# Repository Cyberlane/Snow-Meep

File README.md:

Snow-Meep
=========

Soldering is easy Snow Man variant!

A detailed step by step guide (with pictures) will be available later today.

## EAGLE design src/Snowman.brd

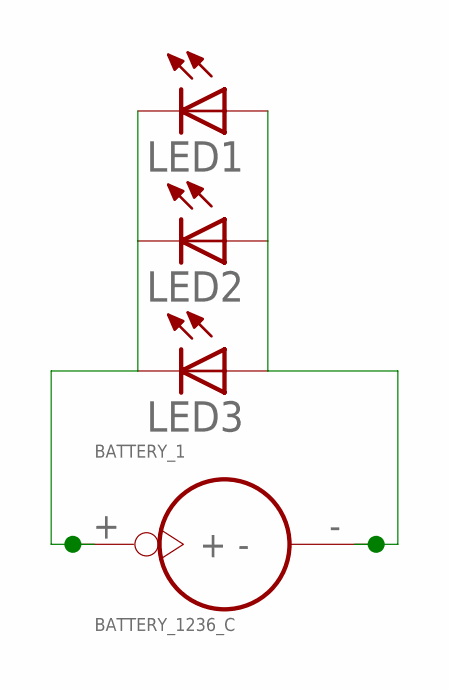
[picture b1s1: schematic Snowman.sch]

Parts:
BATTERY_1: BATTERY_1236_C
LED1, LED2, LED3: LED5MM

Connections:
unnamed: BATTERY_1.+, LED1.K (C), LED2.K (C), LED3.K (C)
unnamed: BATTERY_1.-, LED1.A, LED2.A, LED3.A

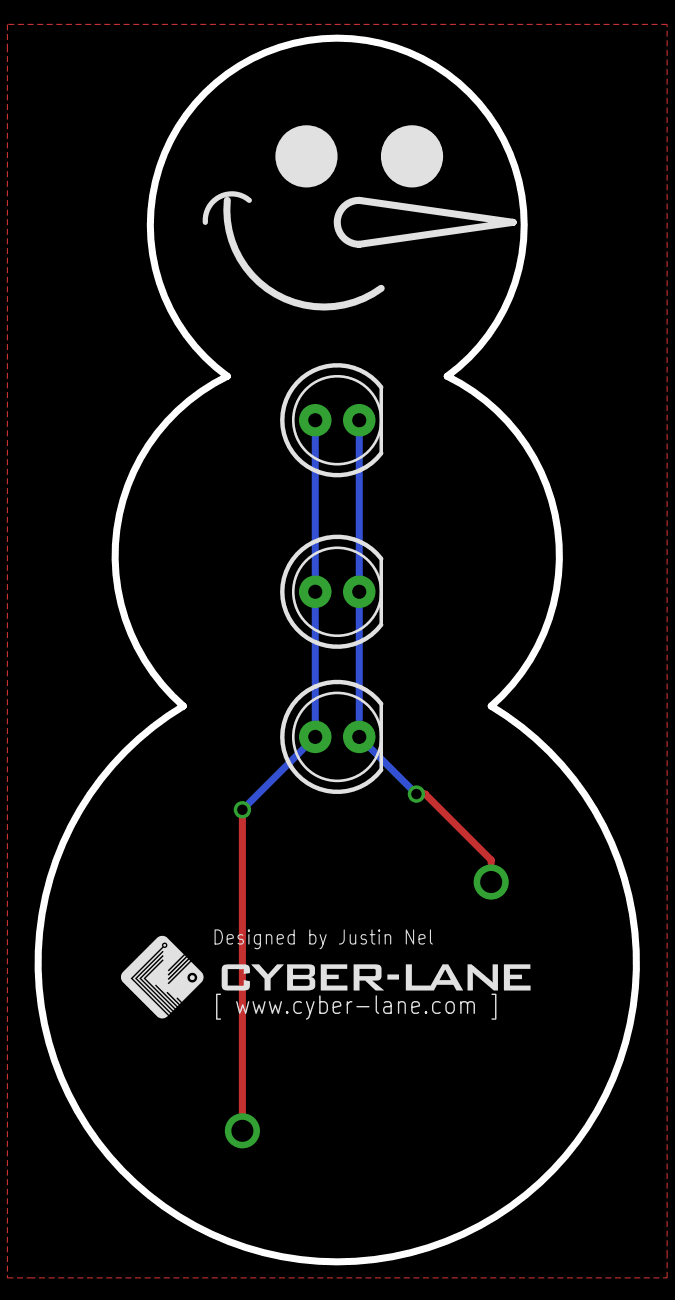
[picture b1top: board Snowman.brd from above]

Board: 2 copper layers, 34.5 x 70.7 mm, 4 parts (1 on the bottom side), 2 nets.

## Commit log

2013-10-30 Version 1 with eagle and gerbers
2013-10-31 Added ground planes
2013-11-02 Corrected a small mistake on the ground planes
2013-11-14 Unsorted assembly pictures
2013-11-14 Rotated one of the assembly pictures
2013-11-16 Added a render of the PCB
2013-11-16 Resized and cropped tutorial images
2013-11-16 Initial tutorial steps
2013-11-16 Updated and re-ordered images
2013-11-17 Updated tutorial
2013-11-17 Updated tutorial image to have labels

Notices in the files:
parts and their libraries:
SparkFun-LED: Licensing: CC v3.0 Share-Alike You are welcome to use this library for commercial purposes.
